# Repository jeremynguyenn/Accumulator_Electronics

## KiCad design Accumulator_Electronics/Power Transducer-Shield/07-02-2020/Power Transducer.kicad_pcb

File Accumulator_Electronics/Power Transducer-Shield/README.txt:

If all the CAD components can't be found in the 3D view is because some parts are referenced to a local folder
in another system. They can be downladed from the "KiCAD Libraries" repository found in Sabin's CADLAB.io account.
There is a link to such account in the team's GitHub, inside the "2021 Accumulator Electronics" repository.

**A component was created out of this PCB. It can be found in this very folder under "Power Transducer Library"

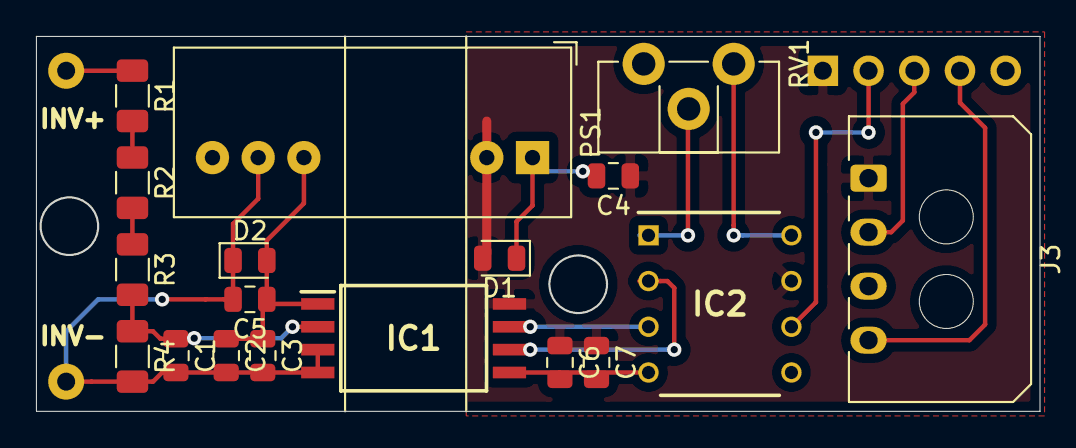
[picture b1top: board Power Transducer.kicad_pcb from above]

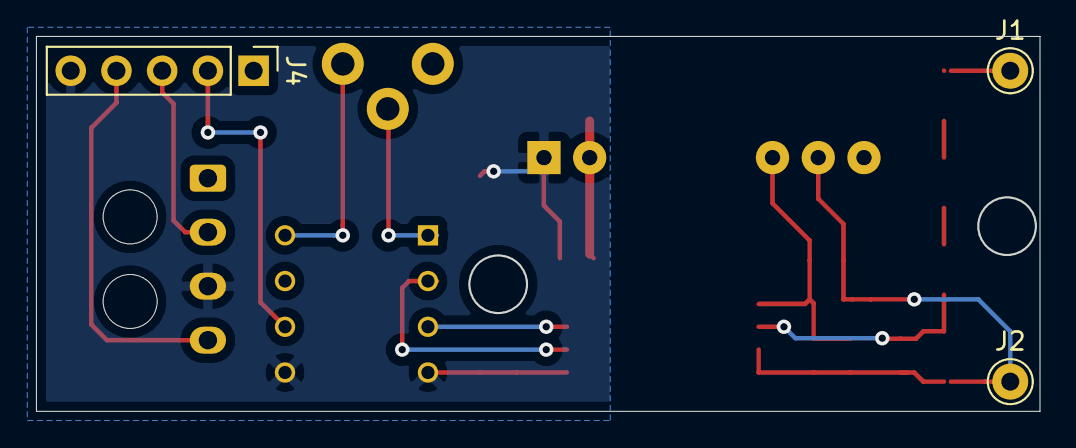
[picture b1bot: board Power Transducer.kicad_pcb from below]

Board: 2 copper layers, 55.8 x 20.8 mm, 21 parts (3 on the bottom side), 15 nets.

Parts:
C1: 10n; C_0805_2012Metric
C2, C7: 1u; C_0805_2012Metric
C3, C4, C5, C6: 0.1u; C_0805_2012Metric
D1, D2: DIODE; D_0805_2012Metric
IC1: AMC1211AQDWVRQ1; SOIC127P1150X280-8N
IC2: INA114AP; DIP794W53P254L959H508Q8N
J1, J2: Conn_01x01; Pin_D1.0mm_L10.0mm
J3: Conn_01x04; Molex_Micro-Fit_3.0_43650-0400_1x04_P3.00mm_Horizontal
J4: Conn_01x05; PinHeader_1x05_P2.54mm_Vertical
PS1: ITX0505SA; Converter_DCDC_XP_POWER-ITXxxxxSA_THT
R1, R2, R3: 3M; R_1206_3216Metric
R4: 59k; R_1206_3216Metric
RV1: 100k; Potentiometer_ACP_CA9-H2,5_Horizontal

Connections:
+5V: C4.1, C6.1, C7.1, D1.2, IC1.8, IC2.7, J3.1, J4.1, PS1.2
GND: C4.2, C6.2, C7.2, D1.1, IC1.5, IC2.4, IC2.5, J3.3, J4.5, PS1.1
HV_Sens: IC2.6, J4.2
High_C_Meas: J3.2, J4.3
Inv+: J1.1, R1.1
Inv-: C1.2, C2.2, C3.2, C5.2, D2.1, IC1.3, IC1.4, J2.1, PS1.7, R4.2
Low_C_Meas: J3.4, J4.4
unnamed: C1.1, IC1.2, R3.2, R4.1
unnamed: IC1.6, IC2.2
unnamed: IC1.7, IC2.3
unnamed: IC2.1, RV1.2
unnamed: IC2.8, RV1.1
unnamed: R1.2, R2.1
unnamed: R2.2, R3.1
VDD1: C2.1, C3.1, C5.1, D2.2, IC1.1, PS1.6

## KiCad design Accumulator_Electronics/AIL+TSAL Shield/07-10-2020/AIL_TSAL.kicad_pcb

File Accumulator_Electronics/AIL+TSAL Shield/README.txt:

If all the CAD components can't be found in the 3D view is because some parts are referenced to a local folder
in another system. They can be downladed from the "KiCAD Libraries" repository found in Sabin's CADLAB.io account.
There is a link to such account in the team's GitHub, inside the "2021 Accumulator Electronics" repository.

**A component was created out of this PCB. It can be found in this very folder under "AIL&TSAL Library"

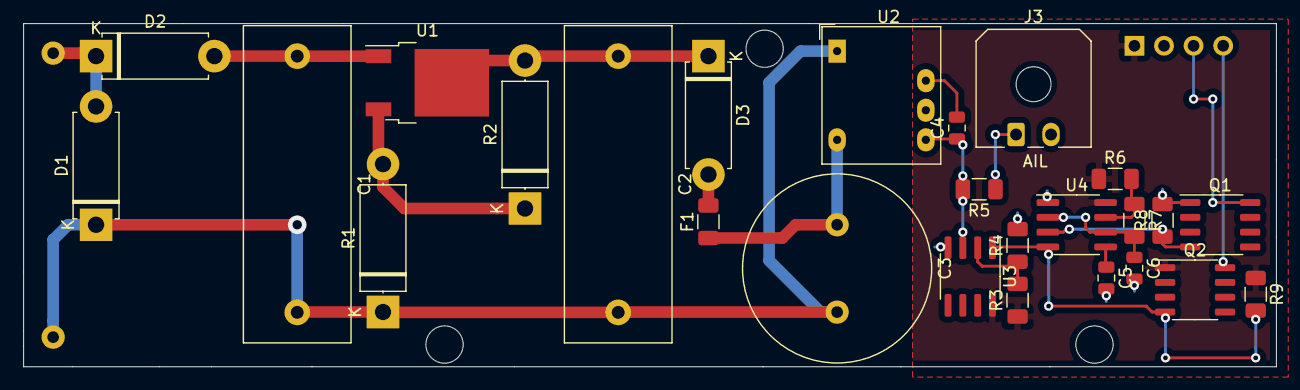
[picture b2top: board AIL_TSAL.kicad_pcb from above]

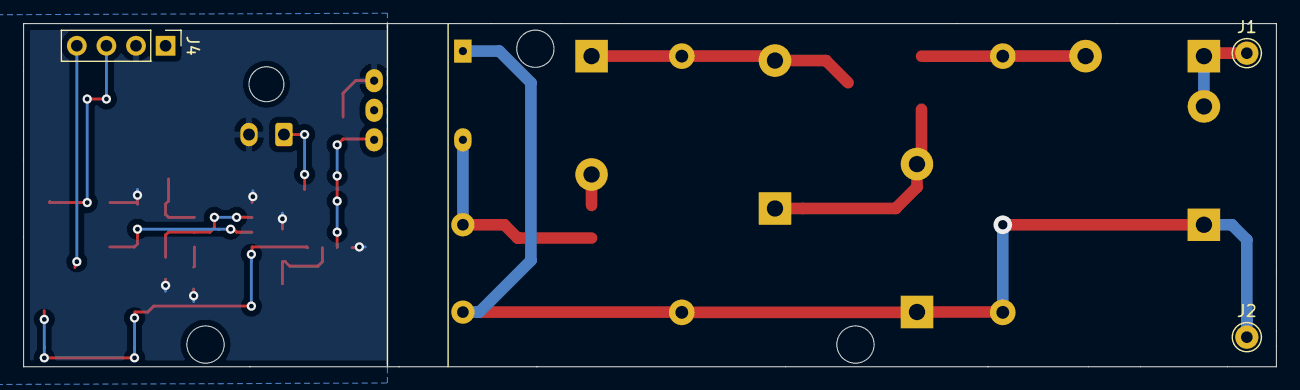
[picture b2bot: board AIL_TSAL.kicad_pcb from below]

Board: 2 copper layers, 107.6 x 29.5 mm, 29 parts (3 on the bottom side), 19 nets.

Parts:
C1: 0.1uF; C_Rect_L27.0mm_W9.0mm_P22.00mm
C2: 1uF; C_Rect_L27.0mm_W9.0mm_P22.00mm
C3: 47uF; C_Radial_D16.0mm_H31.5mm_P7.50mm
C4: 27uF; C_0805_2012Metric
C5: 0.01u; C_0805_2012Metric
C6: 10u; C_0805_2012Metric
D1, D3: DIODE; D_5W_P10.16mm_Horizontal
D2: D_Zener; D_5W_P10.16mm_Horizontal
F1: 50mA; Fuse_1206_3216Metric
J1, J2: Conn_01x01; Pin_D1.0mm_L10.0mm
J3: Conn_01x02; Molex_Micro-Fit_3.0_43650-0200_1x02_P3.00mm_Horizontal
J4: Conn_01x04; PinHeader_1x04_P2.54mm_Vertical
Q1: Q_NMOS_SGD; SO-8_3.9x4.9mm_P1.27mm
Q2: Q_PMOS_SDG; SO-8_3.9x4.9mm_P1.27mm
R1: 48k; D_5W_P12.70mm_Horizontal
R2: 2k; D_5W_P12.70mm_Horizontal
R3, R4, R8, R9: 10k; R_1206_3216Metric
R5: 650; R_1206_3216Metric
R6: 2k; R_1206_3216Metric
R7: 20k; R_1206_3216Metric
U1: LR8K4-G; TO-252-2
U2: CRE1S0505DC; PQP1-D24-D12-D
U3: LM741; SOIC-8_3.9x4.9mm_P1.27mm
U4: LM555; SOIC-8_3.9x4.9mm_P1.27mm

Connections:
+12V: J4.1, Q2.1, R3.1, R6.1, R9.1, U3.8, U4.8
/Sheet5F0851A9/Inv+: D1.2, D2.1, J1.1
/Sheet5F0851A9/Inv-: C1.2, C2.2, C3.2, D1.1, J2.1, R1.1, U2.1
GND: C4.2, C5.2, C6.2, J3.2, J4.2, Q1.1, R4.2, R8.2, U2.7, U3.4, U4.1
Green+: J4.4, Q2.8
unnamed: C1.1, D2.2, U1.1
unnamed: C2.1, D3.1, R2.2, U1.2
unnamed: C3.1, F1.1, U2.4
unnamed: C4.1, R5.2, U2.5, U3.3
unnamed: C5.1, U4.5
unnamed: C6.1, R7.2, U4.2, U4.6
unnamed: D3.2, F1.2
unnamed: J3.1, R5.1
unnamed: Q1.4, R8.1, U4.3
unnamed: Q2.4, R9.2, U3.1, U4.4
unnamed: R1.2, R2.1, U1.3
unnamed: R3.2, R4.1, U3.2
unnamed: R6.2, R7.1, U4.7
Red-: J4.3, Q1.8

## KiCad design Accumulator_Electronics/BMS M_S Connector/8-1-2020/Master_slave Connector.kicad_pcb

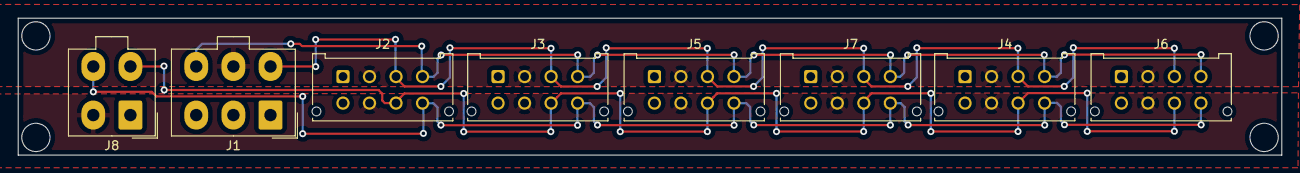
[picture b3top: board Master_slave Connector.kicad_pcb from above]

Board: 2 copper layers, 143.0 x 15.5 mm, 8 parts (0 on the bottom side), 7 nets.

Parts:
J1: Conn_01x06; Molex_Mini-Fit_Jr_5566-06A_2x03_P4.20mm_Vertical
J2, J3, J4, J5, J6, J7: Conn_01x08; Molex_Micro-Fit_3.0_43045-0812_2x04_P3.00mm_Vertical
J8: Conn_01x04; Molex_Mini-Fit_Jr_5566-04A_2x02_P4.20mm_Vertical

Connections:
+12V: J1.5, J2.2, J3.2, J4.2, J5.2, J6.2, J7.2
CANH: J1.4, J2.3, J3.3, J4.3, J5.3, J6.3, J7.3
CANL: J1.6, J2.4, J3.4, J4.4, J5.4, J6.4, J7.4
DCDC+: J2.6, J3.6, J4.6, J5.6, J6.6, J7.6, J8.2
GND: J1.1, J1.2, J2.1, J2.5, J3.1, J3.5, J4.1, J4.5, J5.1, J5.5, J6.1, J6.5, J7.1, J7.5, J8.1
PWM: J2.8, J3.8, J4.8, J5.8, J6.8, J7.8, J8.4
Sens: J2.7, J3.7, J4.7, J5.7, J6.7, J7.7, J8.3

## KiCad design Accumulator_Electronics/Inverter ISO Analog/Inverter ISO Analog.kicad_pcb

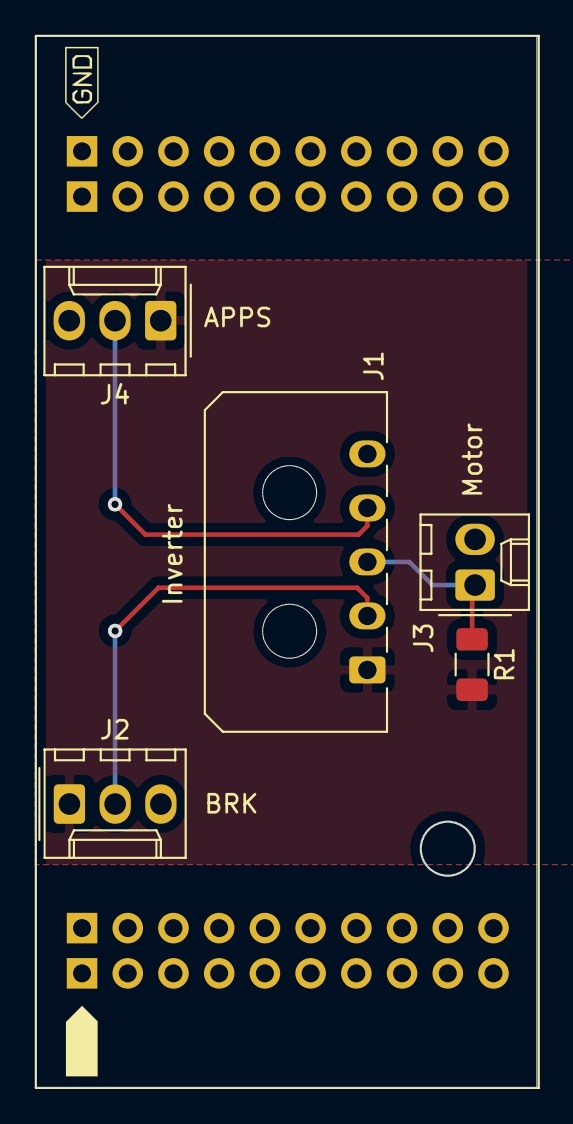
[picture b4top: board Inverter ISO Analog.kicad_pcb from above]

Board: 2 copper layers, 27.8 x 58.4 mm, 6 parts (0 on the bottom side), 5 nets.

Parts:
J1: Inverter; Molex_Micro-Fit_3.0_43650-0500_1x05_P3.00mm_Horizontal
J2: Brake Sensor; Molex_KK-254_AE-6410-03A_1x03_P2.54mm_Vertical
J3: Motor; Molex_KK-254_AE-6410-02A_1x02_P2.54mm_Vertical
J4: Accelerator Sensor; Molex_KK-254_AE-6410-03A_1x03_P2.54mm_Vertical
R1: 330k; R_1206_3216Metric
U1: C2000BoosterPack_Shield

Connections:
+5V: J1.1, J2.1, J4.1, R1.2
APPS: J1.4, J4.2
BRK: J1.2, J2.2
GNDA: J1.5, J2.3, J3.2, J4.3
Therm+: J1.3, J3.1, R1.1

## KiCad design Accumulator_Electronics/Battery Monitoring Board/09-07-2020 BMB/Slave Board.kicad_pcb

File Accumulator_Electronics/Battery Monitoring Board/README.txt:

If all the CAD components can't be found in the 3D view is because some parts are referenced to a local folder
in another system. They can be downladed from the "KiCAD Libraries" repository found in Sabin's CADLAB.io account.
There is a link to such account in the team's GitHub, inside the "2021 Accumulator Electronics" repository.

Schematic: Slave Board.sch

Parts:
C1, C3, C6, C7, C8, C9, C10, C11, C12, C13: 100n; C_0805_2012Metric
C2, C4, C5: 1u; C_0805_2012Metric
D1: DIODE; D_1206_3216Metric
F13: Fuse; Fuse_1206_3216Metric
IC1: LTC6820IMS#PBF; SOP50P490X110-16N; Manufacturer_Part_Number LTC6820IMS#PBF; Mouser Part Number 584-LTC6820IMS#PBF
IC2: LTC6804-2; SOP50P780X200-48N; Manufacturer_Part_Number LTC6804-2
J1, J2, J3, J4, J5, J6, J7, J8, J9, J10, J11, J12: Conn_01x02; TE_MATE-N-LOK_1-770966-x_1x02_P4.14mm_Horizontal
J13: Conn_01x08; Molex_Micro-Fit_3.0_43045-0800_2x04_P3.00mm_Horizontal
J26: Conn_01x01; TE_MATE-N-LOK_1-794374-x_1x01_P4.14mm_Horizontal
J27: Conn_01x04; Molex_KK-254_AE-6410-04A_1x04_P2.54mm_Vertical
Q1: Q_NPN_BCE; SOT-223
R1, R2, R3, R4, R5, R6, R7, R8, R9, R10, R11, R60: 680; R_1206_3216Metric
R12: NC; R_0805_2012Metric
R13: 5k; R_0805_2012Metric
R14, R15, R18, R22, R23: 100; R_0805_2012Metric
R16, R20: 1k21; R_0805_2012Metric
R17, R21: 860; R_0805_2012Metric
R19: 10k; R_0805_2012Metric
T1: PE-68386NL; Pulse_PA2001NL
U1: MCP2551_CANmodule; MCP2515_ArduinoShield
U2: MCP2551-I-SN; SOIC-8_3.9x4.9mm_P1.27mm
U3: OKI-78SR-3.3_1.5-W36-C; SOT-223
U4: ISO1050DUB; SOP-8_6.62x9.15mm_P2.54mm
U5: TMR_1-1212; Converter_DCDC_TRACO_POWER_TEL_10-xxxx_THT
U6: ARDUINO_MICRO_SHIELD; Arduino_Micro_Socket

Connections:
+5V: C1.1, C6.1, C13.1, IC1.1, IC1.6, IC1.7, IC1.8, IC1.9, IC1.12, R1.1, R2.1, R3.1, R4.1, R5.1, R6.1, R7.1, R8.1, R9.1, R10.1, R11.1, R13.1, R60.1, U1.7, U4.8, U6.5V (+5V)
+12V: C7.1, C11.1, D1.2, J13.2, U3.3, U5.2
C0: C2.2, C3.1, C4.2, C5.2, C9.1, IC2.26, IC2.30, IC2.31, IC2.45, IC2.46, IC2.47, IC2.48, R17.1; also elsewhere on the board
C1: IC2.24; also elsewhere on the board
C2: IC2.22; also elsewhere on the board
C3: IC2.20; also elsewhere on the board
C4: IC2.18; also elsewhere on the board
C5: IC2.16; also elsewhere on the board
C6: IC2.14; also elsewhere on the board
C7: IC2.12; also elsewhere on the board
C8: IC2.10; also elsewhere on the board
C9: IC2.8; also elsewhere on the board
C10: IC2.6; also elsewhere on the board
C11: IC2.4; also elsewhere on the board
C12: IC2.2, R22.2; also elsewhere on the board
CANH: J13.3, U2.7
CANL: J13.4, U2.6
CS: IC1.5, R12.1, U1.5, U6.SS (RX_LED/SS)
Cell4: R14.2; also elsewhere on the board
Cell12: F13.2, R22.1, R23.2; also elsewhere on the board
DCDC+: J13.6, J27.2
DRV: IC2.38, Q1.1
GND: C7.2, C8.2, C10.2, C11.2, D1.1, J13.1, J13.5, J27.1, R19.2, U2.2, U3.2, U4.4, U5.1
GND_ISO: C1.2, C6.2, C12.2, C13.2, IC1.13, IC1.14, J1.1, J2.1, J3.1, J4.1, J5.1, J6.1, J7.1, J8.1, J9.1, J10.1, J11.1, J12.1, R21.2, U1.6, U4.5, U5.6, U6.GND
IM: IC1.10, R15.1, T1.3
IMA: IC2.41, R18.1, T1.4
IP: IC1.11, R15.2, T1.1
IPA: IC2.42, R18.2, T1.6
ISO_CANH: U1.8, U4.7
ISO_CANL: U1.9, U4.6
unnamed: C3.2, Q1.2, R14.1
unnamed: C4.1, IC2.35
unnamed: C5.1, IC2.34
unnamed: C9.2, IC2.1, R23.1
unnamed: F13.1, J26.1
unnamed: IC1.15, R20.2, R21.1
unnamed: IC1.16, R20.1
unnamed: IC2.43, R16.1, R17.2
unnamed: IC2.44, R16.2
unnamed: R12.2, U6.TX (1/TX)
unnamed: R19.1, U2.8
PWM_Fans: J13.8, J27.4
RXD: U2.4, U4.2
S1: IC2.25; also elsewhere on the board
S2: IC2.23; also elsewhere on the board
S3: IC2.21; also elsewhere on the board
S4: IC2.19; also elsewhere on the board
S5: IC2.17; also elsewhere on the board
S6: IC2.15; also elsewhere on the board
S7: IC2.13; also elsewhere on the board
S8: IC2.11; also elsewhere on the board
S9: IC2.9; also elsewhere on the board
S10: IC2.7; also elsewhere on the board
S11: IC2.5; also elsewhere on the board
S12: IC2.3; also elsewhere on the board
SCK: IC1.4, U1.2, U6.SCK
SI: IC1.2, U1.3, U6.MO (MOSI)
SO: IC1.3, R13.2, U1.4, U6.MI (MISO)
Sens_Fans: J13.7, J27.3
T0: J1.2, R1.2, U6.A0
T1: J2.2, R2.2, U6.A1
T2: J3.2, R3.2, U6.A2
T3: J4.2, R4.2, U6.A3
T4: J5.2, R5.2, U6.A4
T5: J6.2, R6.2, U6.A5
T6: J7.2, R7.2, U6.4 (4/A6)
T7: J8.2, R8.2, U6.6 (6(PWM)/A7)
T8: J9.2, R9.2, U6.8 (8/A8)
T9: J10.2, R10.2, U6.9 (9(PWM)/A9)
T10: J11.2, R11.2, U6.10 (10(PWM)/A10)
T11: J12.2, R60.2, U6.12 (12/A11)
TXD: U2.1, U4.3
VCC: C8.1, C10.1, U2.3, U3.1, U4.1
VCC_ISO: C12.1, U5.4, U6.VI (VIN)
Vreg: C2.1, IC2.37, IC2.40, Q1.3

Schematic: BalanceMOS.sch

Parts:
C14: 10n; C_0805_2012Metric
F1: Fuse; Fuse_1206_3216Metric
J20: Conn_01x01; TE_MATE-N-LOK_1-794374-x_1x01_P4.14mm_Horizontal
Q2: Q_PMOS_GSD; SOT-23
R24: 3k3; R_0805_2012Metric
R25: 100; R_0805_2012Metric
R26: 33; R_0805_2012Metric

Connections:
C6: C14.2, R25.2; also elsewhere on the board
C7: C14.1; also elsewhere on the board
Cell6: F1.2, R25.1, R26.1; also elsewhere on the board
Cell7: Q2.3; also elsewhere on the board
unnamed 45: F1.1; also elsewhere on the board
unnamed 51: J20.1; also elsewhere on the board
unnamed: Q2.1, R24.1
unnamed: Q2.2, R26.2
S7: R24.2; also elsewhere on the board

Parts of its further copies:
C15, C16, C17, C18, C19, C20, C21, C22, C23, C24, C25: 10n; C_0805_2012Metric
F2, F3, F4, F5, F6, F7, F8, F9, F10, F11, F12: Fuse; Fuse_1206_3216Metric
J14, J15, J16, J17, J18, J19, J21, J22, J23, J24, J25: Conn_01x01; TE_MATE-N-LOK_1-794374-x_1x01_P4.14mm_Horizontal
Q3, Q4, Q5, Q6, Q7, Q8, Q9, Q10, Q11, Q12, Q13: Q_PMOS_GSD; SOT-23
R27, R30, R33, R36, R39, R42, R45, R48, R51, R54, R57: 3k3; R_0805_2012Metric
R28, R31, R34, R37, R40, R43, R46, R49, R52, R55, R58: 100; R_0805_2012Metric
R29, R32, R35, R38, R41, R44, R47, R50, R53, R56, R59: 33; R_0805_2012Metric

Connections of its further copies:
C0: C20.2, R43.2; also elsewhere on the board
C1: C20.1, C21.2, R46.2; also elsewhere on the board
C2: C21.1, C22.2, R49.2; also elsewhere on the board
C3: C22.1, C23.2, R52.2; also elsewhere on the board
C4: C23.1, C24.2, R55.2; also elsewhere on the board
C5: C24.1, C25.2, R58.2; also elsewhere on the board
C6: C25.1; also elsewhere on the board
C7: C15.2, R28.2; also elsewhere on the board
C8: C15.1, C16.2, R31.2; also elsewhere on the board
C9: C16.1, C17.2, R34.2; also elsewhere on the board
C10: C17.1, C18.2, R37.2; also elsewhere on the board
C11: C18.1, C19.2, R40.2; also elsewhere on the board
C12: C19.1; also elsewhere on the board
Cell0: F7.2, R43.1, R44.1
Cell1: F8.2, Q8.3, R46.1, R47.1
Cell2: F9.2, Q9.3, R49.1, R50.1
Cell3: F10.2, Q10.3, R52.1, R53.1
Cell4: F11.2, Q11.3, R55.1, R56.1; also elsewhere on the board
Cell5: F12.2, Q12.3, R58.1, R59.1
Cell6: Q13.3; also elsewhere on the board
Cell7: F2.2, R28.1, R29.1; also elsewhere on the board
Cell8: F3.2, Q3.3, R31.1, R32.1
Cell9: F4.2, Q4.3, R34.1, R35.1
Cell10: F5.2, Q5.3, R37.1, R38.1
Cell11: F6.2, Q6.3, R40.1, R41.1
Cell12: Q7.3; also elsewhere on the board
unnamed 45: J14.1; also elsewhere on the board
unnamed: F2.1, J15.1
unnamed: F3.1, J16.1
unnamed: F4.1, J17.1
unnamed: F5.1, J18.1
unnamed: F6.1, J19.1
unnamed 51: F7.1; also elsewhere on the board
unnamed: F8.1, J21.1
unnamed: F9.1, J22.1
unnamed: F10.1, J23.1
unnamed: F11.1, J24.1
unnamed: F12.1, J25.1
unnamed: Q3.1, R27.1
unnamed: Q3.2, R29.2
unnamed: Q4.1, R30.1
unnamed: Q4.2, R32.2
unnamed: Q5.1, R33.1
unnamed: Q5.2, R35.2
unnamed: Q6.1, R36.1
unnamed: Q6.2, R38.2
unnamed: Q7.1, R39.1
unnamed: Q7.2, R41.2
unnamed: Q8.1, R42.1
unnamed: Q8.2, R44.2
unnamed: Q9.1, R45.1
unnamed: Q9.2, R47.2
unnamed: Q10.1, R48.1
unnamed: Q10.2, R50.2
unnamed: Q11.1, R51.1
unnamed: Q11.2, R53.2
unnamed: Q12.1, R54.1
unnamed: Q12.2, R56.2
unnamed: Q13.1, R57.1
unnamed: Q13.2, R59.2
S1: R42.2; also elsewhere on the board
S2: R45.2; also elsewhere on the board
S3: R48.2; also elsewhere on the board
S4: R51.2; also elsewhere on the board
S5: R54.2; also elsewhere on the board
S6: R57.2; also elsewhere on the board
S8: R27.2; also elsewhere on the board
S9: R30.2; also elsewhere on the board
S10: R33.2; also elsewhere on the board
S11: R36.2; also elsewhere on the board
S12: R39.2; also elsewhere on the board

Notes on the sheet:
Resistor between C0 and Cell0 is a SC

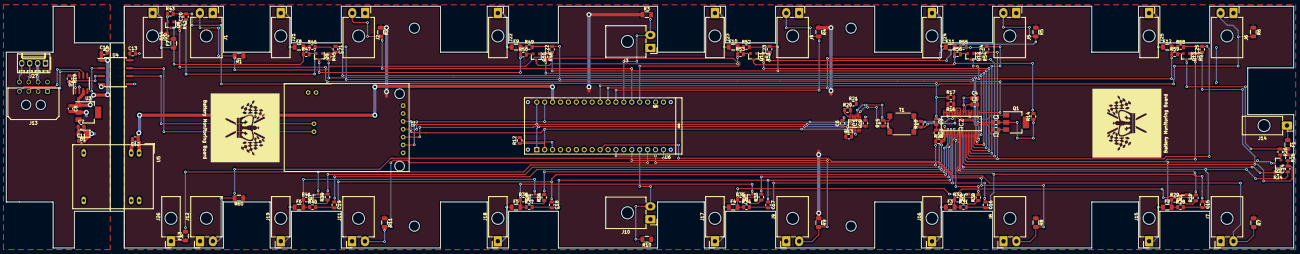
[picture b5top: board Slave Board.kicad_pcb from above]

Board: 2 copper layers, 412.7 x 77.5 mm, 148 parts (0 on the bottom side), 122 nets.

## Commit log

2025-11-17 Create LICENSE
